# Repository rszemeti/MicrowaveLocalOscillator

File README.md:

# MicrowaveLocalOscillator

[![CC BY-SA 4.0][cc-by-sa-shield]][cc-by-sa]

## Description

A simple 2 stage microwave local oscillator using an ADF 4153 to control a Crystek (or similar) VCO

A OCXO reference oscillator is optionally controlled by an ADF4001 when a 10MHz reference signal is present.

## License 

This work is licensed under a
[Creative Commons Attribution-ShareAlike 4.0 International License][cc-by-sa].

[![CC BY-SA 4.0][cc-by-sa-image]][cc-by-sa]

[cc-by-sa]: http://creativecommons.org/licenses/by-sa/4.0/
[cc-by-sa-image]: https://licensebuttons.net/l/by-sa/4.0/88x31.png
[cc-by-sa-shield]: https://img.shields.io/badge/License-CC%20BY--SA%204.0-lightgrey.svg

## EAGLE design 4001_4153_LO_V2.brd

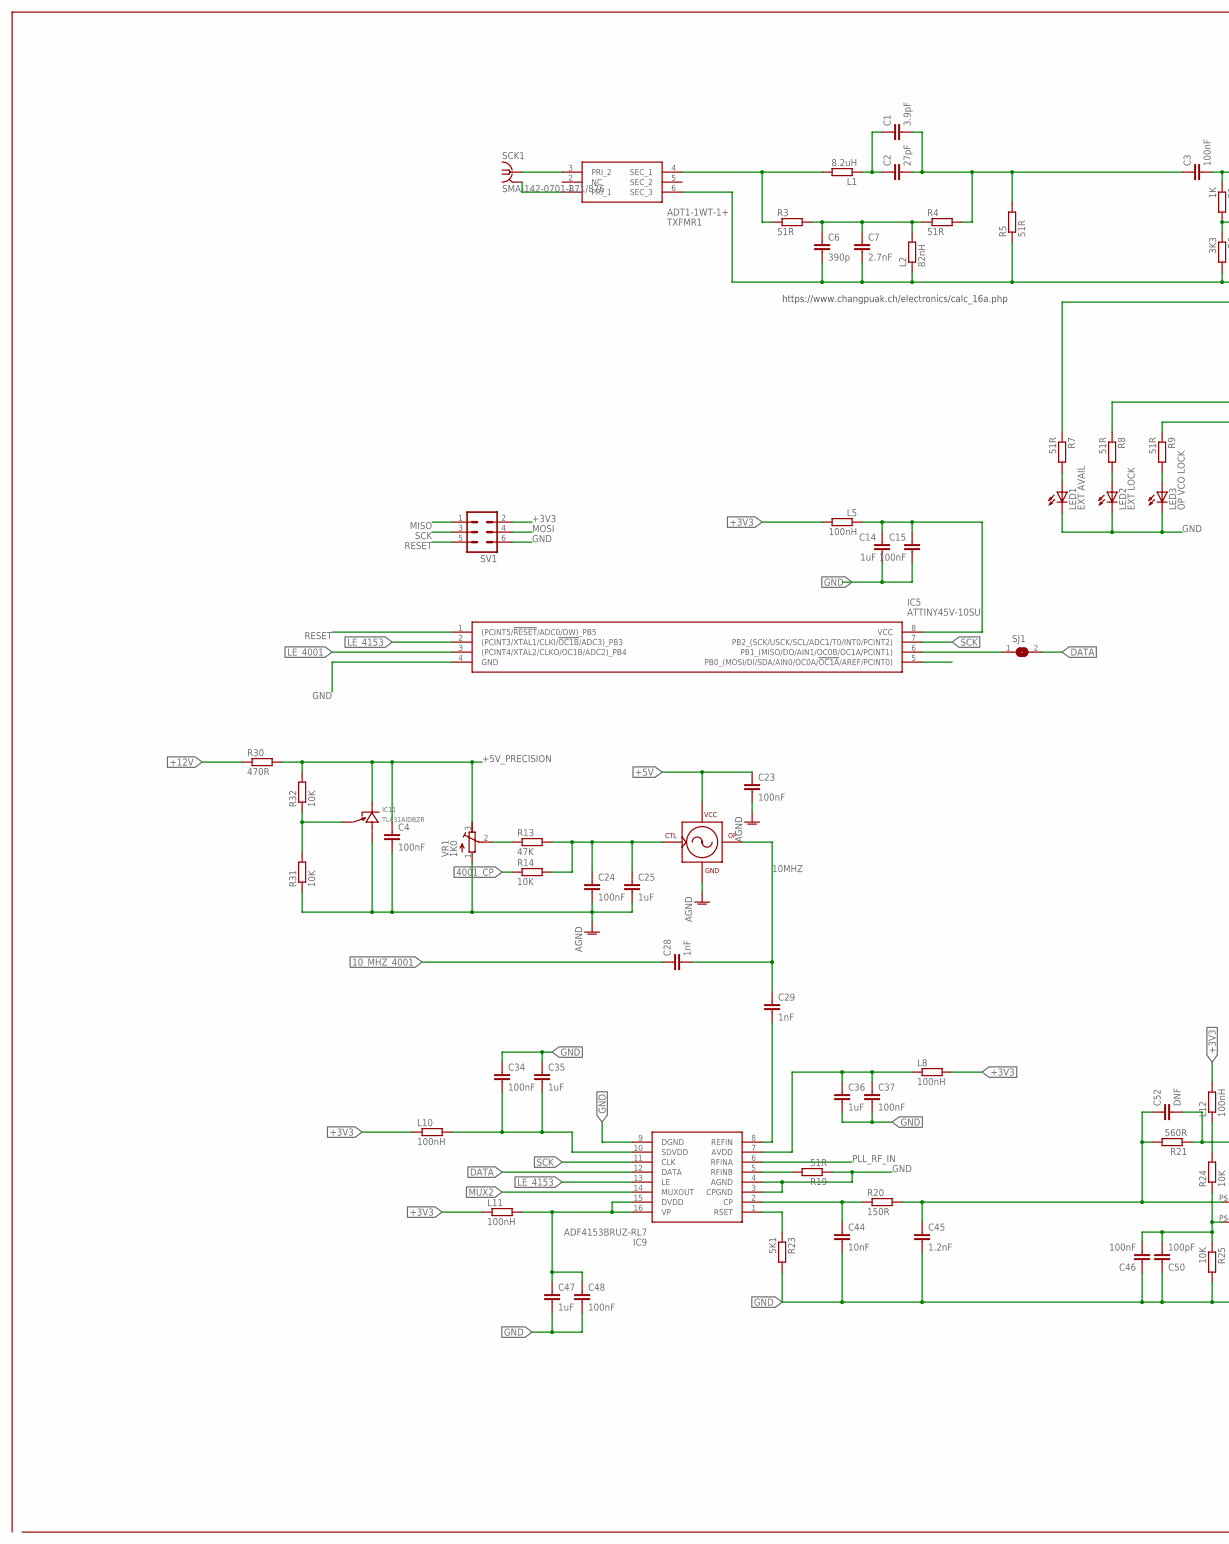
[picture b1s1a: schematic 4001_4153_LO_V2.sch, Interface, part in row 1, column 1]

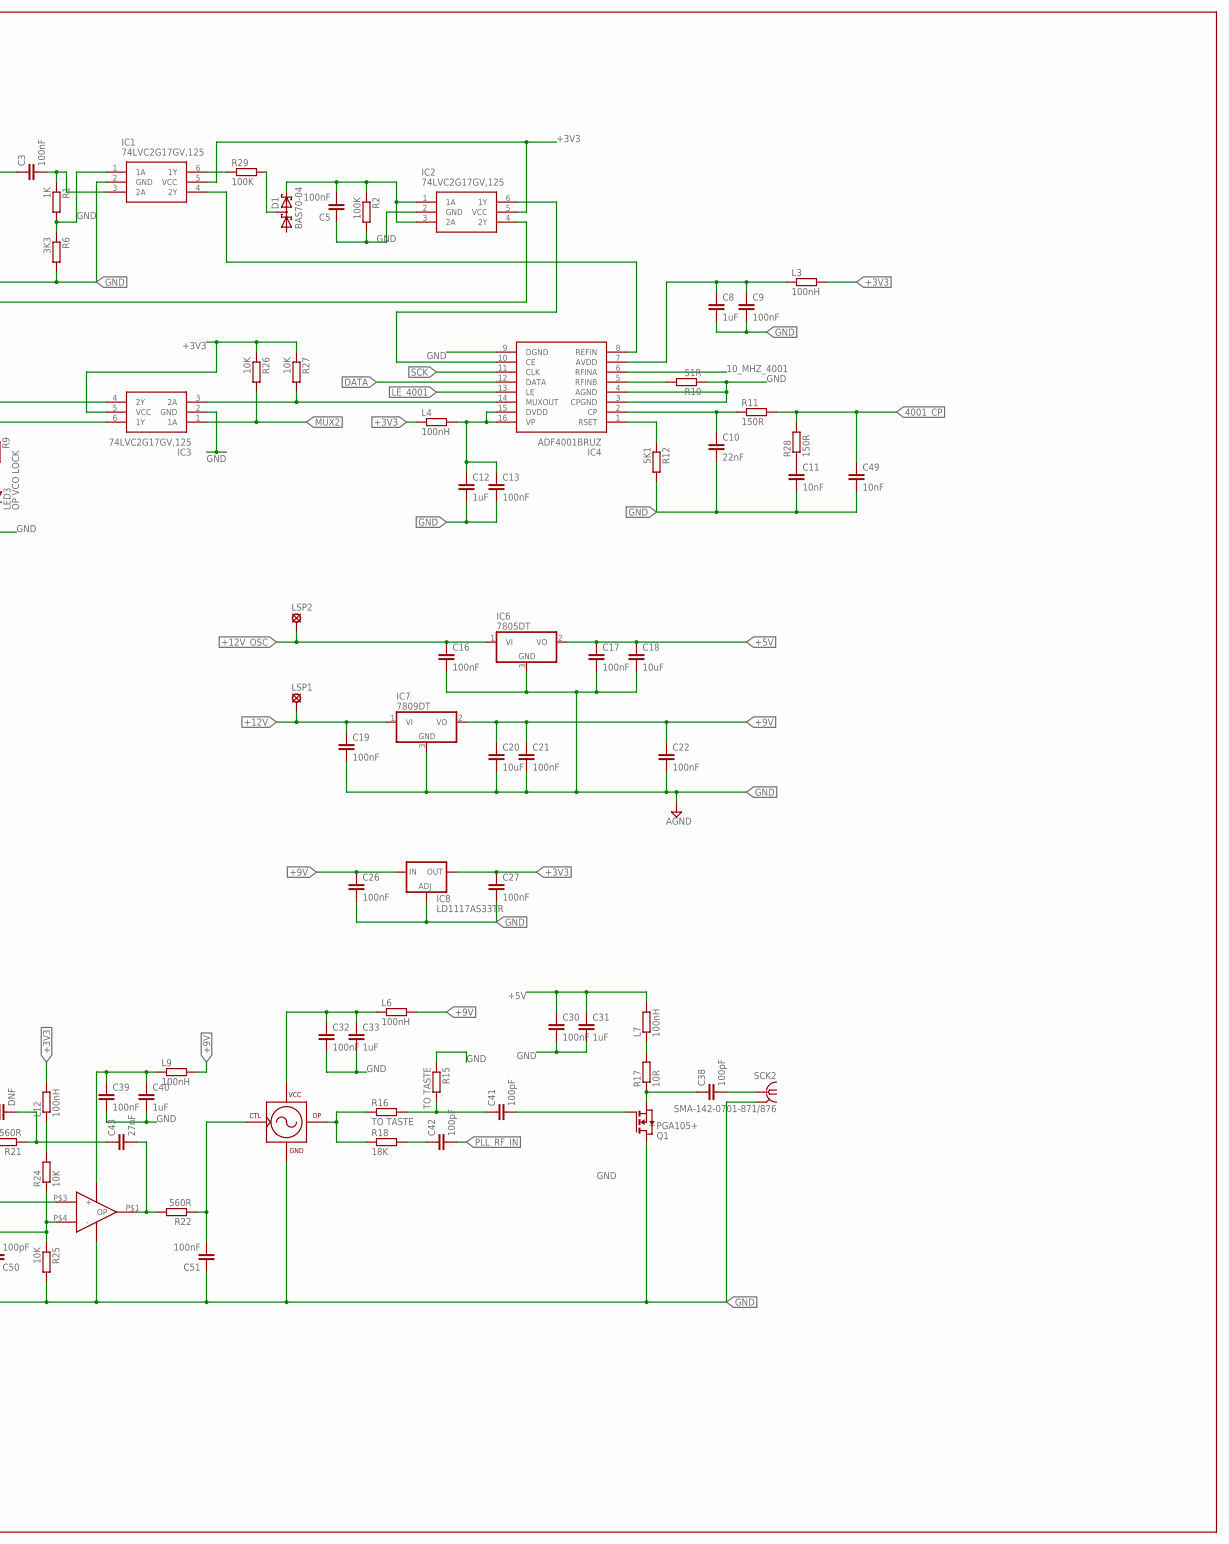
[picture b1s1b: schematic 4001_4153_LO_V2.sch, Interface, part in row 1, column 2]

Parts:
C1: 3.9pF; C0603
C2: 27pF; C0603
C3, C4, C5, C9, C13, C15, C23, C24, C30, C32, C34, C37, C39, C46, C48, C51: 100nF; C0603
C6: 390p; C0603
C7: 2.7nF; C0603
C8, C12, C14, C25, C31, C33, C35, C36, C40, C47: 1uF; C0603
C10: 22nF; C0603
C11, C44, C49: 10nF; C0603
C16, C17, C19, C21, C22, C26, C27: 100nF; C0805
C18, C20: 10uF; C0805
C28, C29: 1nF; C0603
C38, C41, C42, C50: 100pF; C0603
C43: 27nF; C0603
C45: 1.2nF; C0603
C52: DNF; C0603
D1: BAS70-04; SOT23
IC1: 74LVC2G17GV,125; SOT95P275X110-6N
IC2, IC3: 74LVC2G17GV,125; SOT95P275X110-6N; MANUFACTURER_PART_NUMBER 74LVC2G17GV,125; MOUSER_PART_NUMBER 771-74LVC2G17GV-G
IC4: ADF4001BRUZ; SOP65P640X120-16N; JLC C207717
IC5: ATTINY45V-10SU; SOIC127P798X216-8N
IC6: 7805DT; TO252
IC7: 7809DT; TO252
IC8: LD1117AS33TR; SOT223; JLC C108495
IC9: ADF4153BRUZ-RL7; SOP65P640X120-16N
IC10: MCP6H01T-E/LT; SOT23-5; MPN MCP6H01T-E/LT
IC11: TL431AIDBZR; SOT23L
L1: 8.2uH; R0603
L2: 82nH; R0603
L3, L4, L5, L6, L7, L8, L9, L10, L11, L12: 100nH; R0603
LED1: EXT AVAIL; LED3MM
LED2: EXT LOCK; LED3MM
LED3: OP VCO LOCK; LED3MM
LSP1, LSP2: LSP13
OSC1: CTI_OSC
OSC2: CRSYTELEK_127; CRYSTEK_VCO
Q1: PGA105+; SOT89
R1: 1K; R0603
R2, R29: 100K; R0603
R3, R4, R5, R7, R8, R9, R10, R19: 51R; R0603
R6: 3K3; R0603
R11, R20, R28: 150R; R0603
R12, R23: 5K1; R0603
R13: 47K; R0603
R14, R24, R25, R26, R27, R31, R32: 10K; R0603
R15, R16: TO TASTE; R0603
R17: 10R; R0603
R18: 18K; R0603
R21, R22: 560R; R0603
R30: 470R; R0603
SCK1: SMA-142-0701-871/876; J502-ND-142-0701-871/876
SCK2: SMA-142-0701-871/876; J502-ND-142-0701-871/876; MPN 142-0701-871
SJ1: SJ
SV1: ML6; MPN MC-254-06-00-ST-DIP
TXFMR1: ADT1-1WT-1+; SOP254P691X284-6N
VR1: 1K0; RTRIM64Y; MPN 3296Y-1-103LF

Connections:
10MHZ: C28.2, C29.1, OSC1.OUT (OP)
10MHZ_REF: C29.2, IC9.8 (REFIN)
10_MHZ_4001: C28.1, IC4.6 (RFINA)
4001_CP: C49.1, R11.2, R14.1, R28.2
+3V3: C27.1, IC1.5 (VCC), IC2.5 (VCC), IC3.5 (VCC), IC8.4 (OUT), L3.2, L4.1, L5.2, L8.2, L10.1, L11.1, L12.2, R26.1, R27.1, SV1.2
+5V: C17.1, C18.1, C23.1, C30.1, C31.1, IC6.2 (VO), L7.2, OSC1.VCC
+5V_PRECISION: C4.1, IC11.G (CATHODE), R30.2, R32.2, VR1.3 (A)
+8V: C32.1, C33.1, L6.1, OSC2.P$14 (VCC)
+9V: C20.1, C21.1, C22.1, C26.1, IC7.2 (VO), IC8.3 (IN), L6.2, L9.2
+12V: C19.1, IC7.1 (VI), LSP1.MP, R30.1
+12V_OSC: C16.1, IC6.1 (VI), LSP2.MP
AVDD: C36.1, C37.1, IC9.7 (AVDD), L8.1
DATA: IC4.12 (DATA), IC9.12 (DATA), SJ1.2
DVDD: C47.1, C48.1, IC9.15 (DVDD), IC9.16 (VP), L11.2
DVDD1: C12.1, C13.1, IC4.15 (DVDD), IC4.16 (VP), L4.2
FILT_EXT_REF: C1.2, C2.2, C3.1, R4.2, R5.2
GND: C4.2, C5.1, C6.2, C7.2, C8.2, C9.2, C10.2, C11.2, C12.2, C13.2, C14.2, C15.2, C16.2, C17.2, C18.2, C19.2, C20.2, C21.2, C22.2, C23.2, C24.2, C25.2, C26.2, C27.2, C30.2, C31.2, C32.2, C33.2, C34.1, C35.1, C36.2, C37.2, C39.2, C40.2, C44.2, C45.2, C46.1, C47.2, C48.2, C49.2, C50.1, C51.1, IC1.2 (GND), IC2.2 (GND), IC3.2 (GND), IC4.3 (CPGND), IC4.4 (AGND), IC4.9 (DGND), IC5.4 (GND), IC6.3 (GND), IC7.3 (GND), IC8.1 (ADJ), IC9.3 (CPGND), IC9.4 (AGND), IC9.9 (DGND), IC10.P$2 (-VE), IC11.D (ANODE), L2.1, LED1.K (C), LED2.K (C), LED3.K (C), OSC1.GND, OSC2.P$1 (GND), OSC2.P$3 (GND), OSC2.P$4 (GND), OSC2.P$5 (GND), OSC2.P$6 (GND), OSC2.P$7 (GND), OSC2.P$8 (GND), OSC2.P$9 (GND), OSC2.P$11 (GND), OSC2.P$12 (GND), OSC2.P$13 (GND), OSC2.P$15 (GND), OSC2.P$16 (GND), Q1.2 (D), R2.2, R5.1, R6.2, R10.1, R12.2, R15.1, R19.1, R23.2, R25.2, R31.1, SCK1.G@1 (GND), SCK1.G@2 (GND), SCK1.G@3 (GND), SCK1.G@4 (GND), SCK2.G@1 (GND), SCK2.G@2 (GND), SCK2.G@3 (GND), SCK2.G@4 (GND), SV1.6, TXFMR1.1 (PRI_1), TXFMR1.6 (SEC_3), VR1.1 (E)
LE_4001: IC4.13 (LE), IC5.3 ((PCINT4/XTAL2/CLKO/OC1B/ADC2)_PB4)
LE_4153: IC5.2 ((PCINT3/XTAL1/CLKI/!OC1B!/ADC3)_PB3), IC9.13 (LE)
LOOP_IN: C45.1, C52.1, IC10.P$3 (+), R20.2, R21.2
MISO: IC5.6 (PB1_(MISO/DO/AIN1/OC0B/OC1A/PCINT1)), SJ1.1, SV1.1
MOSI: IC5.5 (PB0_(MOSI/DI/SDA/AIN0/OC0A/!OC1A!/AREF/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), SV1.4
MUX2: IC3.1 (1A), IC9.14 (MUXOUT), R26.2
unnamed: IC9.5 (RFINB), R19.2
unnamed: IC9.1 (RSET), R23.1
unnamed: C39.1, C40.1, IC10.P$6 (+VE), L9.1
unnamed: OSC2.P$10 (OP), R16.1, R18.1
unnamed: C46.2, C50.2, IC10.P$4 (-), R24.1, R25.1
unnamed: IC4.5 (RFINB), R10.2
unnamed: C43.1, C52.2, R21.1
unnamed: C43.2, IC10.P$1 (OP), R22.2
unnamed: C42.1, R18.2
unnamed: C41.2, Q1.1 (G)
unnamed: C38.1, Q1.3 (S), R17.1
unnamed: C41.1, R15.2, R16.2
unnamed: IC4.1 (RSET), R12.1
unnamed: C10.1, IC4.2 (CP), R11.1
unnamed: C44.1, IC9.2 (CP), R20.1
unnamed: C3.2, IC1.3 (2A), R1.1
unnamed: LED3.A, R9.2
unnamed: R13.1, VR1.2 (S)
unnamed: IC3.4 (2Y), R8.1
unnamed: L7.1, R17.2
unnamed: C11.1, R28.1
unnamed: D1.3 (C1A2), R29.2
unnamed: C5.2, D1.2 (C2), IC2.1 (1A), IC2.3 (2A), R2.1
unnamed: LED2.A, R8.2
unnamed: IC3.3 (2A), IC4.14 (MUXOUT), R27.2
unnamed: IC3.6 (1Y), R9.1
unnamed: LED1.A, R7.2
unnamed: IC2.4 (2Y), R7.1
unnamed: IC1.6 (1Y), R29.1
unnamed: C1.1, C2.1, L1.1
unnamed: C24.1, C25.1, OSC1.REF (CTRL), R13.2, R14.2
unnamed: L1.2, R3.1, TXFMR1.4 (SEC_1)
unnamed: SCK1.1, TXFMR1.3 (PRI_2)
unnamed: C6.1, C7.1, L2.2, R3.2, R4.1
unnamed: C8.1, C9.1, IC4.7 (AVDD), L3.1
unnamed: IC1.1 (1A), R1.2, R6.1
unnamed: IC1.4 (2Y), IC4.8 (REFIN)
unnamed: L12.1, R24.2
unnamed: C51.2, OSC2.P$2 (CTRL), R22.1
unnamed: IC11.S (CTRL), R31.2, R32.1
OUTPUT: C38.2, SCK2.1
PLL_RF_IN: C42.2, IC9.6 (RFINA)
RESET: IC5.1 ((PCINT5/!RESET!/ADC0/DW)_PB5), SV1.5
SCK: IC4.11 (CLK), IC5.7 (PB2_(SCK/USCK/SCL/ADC1/T0/INT0/PCINT2)), IC9.11 (CLK), SV1.3
SDVDD: C34.2, C35.2, IC9.10 (SDVDD), L10.2
SDVDD1: IC2.6 (1Y), IC4.10 (CE)
VCC_UP: C14.1, C15.1, IC5.8 (VCC), L5.1

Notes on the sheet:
https://www.changpuak.ch/electronics/calc_16a.php

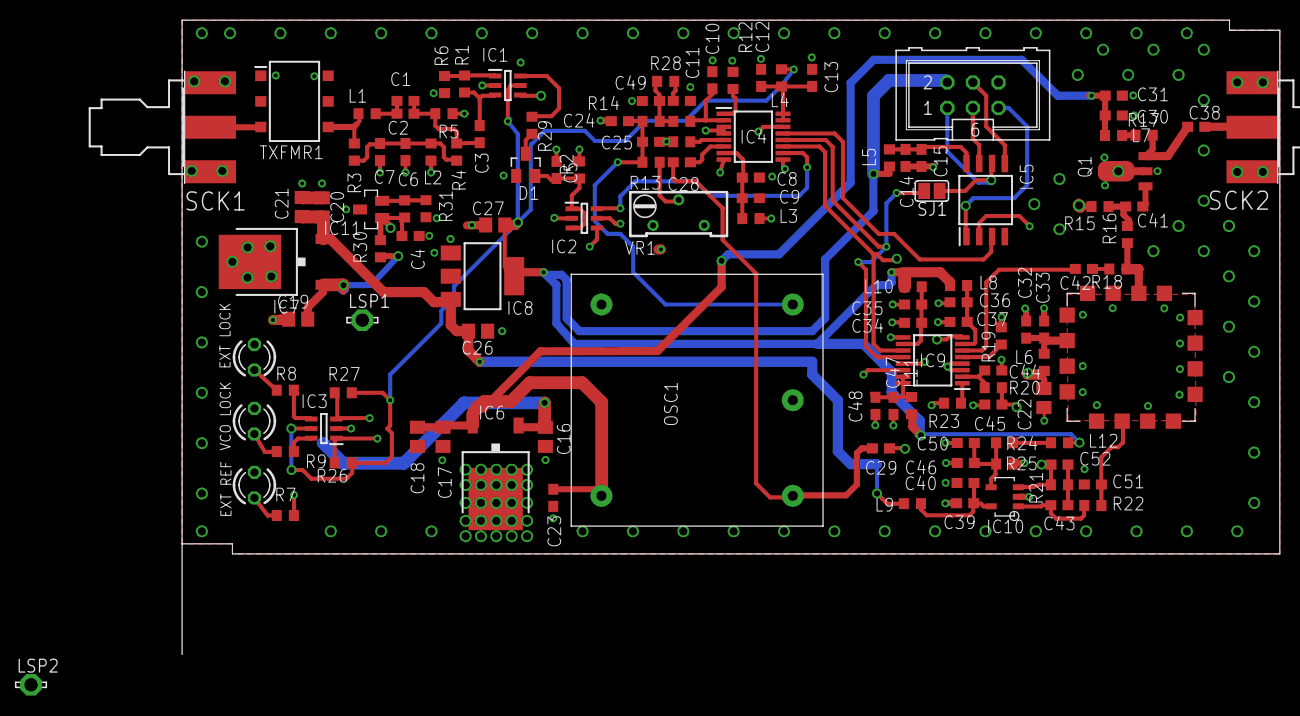
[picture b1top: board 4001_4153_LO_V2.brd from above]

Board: 4 copper layers, 109.0 x 53.0 mm, 122 parts (0 on the bottom side), 70 nets.

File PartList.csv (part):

Partlist

Exported from 4001_4153_LO_V2.brd at 26/11/2022 21:42:16

EAGLE Version 6.2.0 Copyright (c) 1988-2012 CadSoft

Assembly variant: 

Part     Value                Package                  Library         Position (mm)         Orientation

C1       3.9pF                C0603                    resistor        (22.184 44.983)       R0
C2       27pF                 C0603                    resistor        (22.184 43.713)       R0
C3       100nF                C0603                    resistor        (29.55 41.681)        R90
C5       100nF                C0603                    resistor        (37.17 38.125)        R270
C6       390p                 C0603                    resistor        (22.184 39.903)       R270
C7       2.7nF                C0603                    resistor        (19.644 39.903)       R270
C8       1uF                  C0603                    resistor        (56.474 37.363)       R0
C9       100nF                C0603                    resistor        (56.474 35.331)       R0
C10      22nF                 C0603                    resistor        (52.6538 47.031)      R90
C11      10nF                 C0603                    resistor        (49.616 44.983)       R0
C12      1uF                  C0603                    resistor        (57.49 47.269)        R90
C13      100nF                C0603                    resistor        (62.554 47.269)       R90
C14      1uF                  C0603                    resistor        (71.823 39.3165)      R270
C15      100nF                C0603                    resistor        (73.4105 39.3165)     R270
C16      100nF                C0805                    rcl             (36.07 11.625)        R270
C17      100nF                C0805                    rcl             (25.91 11.625)        R270
C18      10uF                 C0805                    rcl             (23.37 11.625)        R270
C19      100nF                C0805                    rcl             (14.219796875 22.414459375) R270
C20      10uF                 C0805                    rcl             (19.40608125 23.082025) R0
C21      100nF                C0805                    rcl             (19.442696875 25.072253125) R0
C22      100nF                C0805                    rcl             (85.571778125 15.481146875) R270
C23      100nF                C0603                    rcl             (49.6414 30.2002)     R180
C24      100nF                C0603                    rcl             (43.47164375 42.96926875) R180
C25      1uF                  C0603                    rcl             (46.568 40.919)       R0
C26      100nF                C0805                    rcl             (29.389134375 22.11664375) R0
C27      100nF                C0805                    rcl             (31.09234375 32.661259375) R180
C28      1nF                  C0603                    resistor        (49.616 38.887)       R180
C29      1nF                  C0603                    resistor        (78.607853125 11.519221875) R180
C30      100nF                C0603                    resistor        (92.5032375 43.536478125) R0
C31      1uF                  C0603                    resistor        (92.511296875 45.5050375) R0
C32      100nF                C0603                    resistor        (83.816090625 22.27368125) R90
C33      1uF                  C0603                    resistor        (85.58979375 22.28625625) R90
C34      100nF                C0603                    resistor        (72.587615625 22.950003125) R0
C35      1uF                  C0603                    resistor        (72.59211875 24.756921875) R0
C36      1uF                  C0603                    resistor        (77.10156875 24.97775) R180
C37      100nF                C0603                    resistor        (77.104415625 23.03903125) R180
C38      100pF                C0603                    resistor        (100.6980125 42.4133375) R0
C39      100nF                C0603                    resistor        (98.269059375 8.22005625) R0
C40      1uF                  C0603                    resistor        (98.29523125 9.993734375) R0
C41      100pF                C0603                    resistor        (94.5482 34.492921875) R0
C42      100pF                C0603                    resistor        (89.541459375 28.29810625) R180
C43      6.8nF                C0603                    resistor        (88.940515625 8.28975625) R0
C44      22nF                 C0603                    resistor        (80.545046875 18.214171875) R0
C45      10nF                 C0603                    resistor        (80.551871875 14.826984375) R180
C46      15nF                 C0603                    resistor        (88.93343125 4.39005) R0
C47      1uF                  C0603                    resistor        (70.62865625 14.704671875) R270
C48      100nF                C0603                    resistor        (68.841971875 14.70188125) R270
C49      10nF                 C0603                    resistor        (46.5468 44.971)      R180
D1       BAS70-04             SOT23                    diode           (34.122 38.633)       R0
IC1      74LVC2G17GV,125      SOT95P275X110-6N         74LVC2G17GV_125 (32.344 46.507)       R0
IC2      74LVC2G17GV,125      SOT95P275X110-6N         74LVC2G17GV_125 (39.946 33.323)       R0
IC3      74LVC2G17GV,125      SOT95P275X110-6N         74LVC2G17GV_125 (14.074 12.447)       R180
IC4      ADF4001BRUZ          SOP65P640X120-16N        ADF4001BRUZ     (56.728 41.427)       R0
IC5      ATTINY45V-10SU       SOIC127P798X216-8N       ATTINY45V-10SU  (79.79 35.137)        R90
IC6      7805DT               TO252                    linear          (31.136 7.947)        R180
IC7      7809DT               TO252                    linear          (13.994 27.759)       R0
IC8      LD1117AS33TR         SOT223                   v-reg           (29.83038125 27.5757625) R270
IC9      ADF4153BRUZ-RL7      SOP65P640X120-16N        ADF4153BRUZ-RL7 (74.531103125 19.22043125) R180
IC10     MCP6H01              SOT23-5                  RF              (94.32 7.3275)        R0
L1       8.2uH                R0603                    resistor        (18.374 43.713)       R180
L2       82nH                 R0603                    resistor        (24.724 39.903)       R90
L3       100nH                R0603                    resistor        (56.474 33.299)       R0
L4       100nH                R0603                    resistor        (59.522 47.269)       R270
L5       100nH                R0603                    resistor        (70.2355 39.3165)     R270
L6       100nH                R0603                    resistor        (85.601953125 19.025) R270
L7       100nH                R0603                    resistor        (92.484778125 41.541925) R180
L8       100nH                R0603                    resistor        (77.094775 26.646446875) R180
L9       100nH                R0603                    resistor        (98.232809375 5.972478125) R0
L10      100nH                R0603                    resistor        (72.5892375 26.526909375) R0
L11      100nH                R0603                    resistor        (72.418071875 14.728709375) R90
LED1     EXT AVAIL            LED3MM                   led             (7.184 6.827)         R90
LED2     EXT LOCK             LED3MM                   led             (7.184 19.527)        R90
LED3     OP VCO LOCK          LED3MM                   led             (7.184 13.177)        R90
LSP1     LSP13                LSP13                    solpad          (7.42 26.695)         R0
OSC1     CTI_OSC              CTI_OSC                  RF              (51.14 15.265)        R90
OSC2     CRSYTELEK_127        CRYSTEK_VCO              RF              (87.880125 13.1765375) R0
Q1       PGA105+              SOT89                    zetex           (93.685 37.998)       R90
R1       1K                   R0603                    rcl             (28.04 46.663)        R90
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
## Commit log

2022-11-25 Add files via upload
    Initial Commit
2022-11-25 Size change and pre-release tweaks
    Updated sizes, sorted out component name positions on PCB, added 10R to PGA105+drive ref Andy JNT
2022-11-25 Renumber
    Renumbered all components
2022-11-25 Removed backup files
    ...
2022-11-25 Gerbers for test boards
    Layer stack sorted out, gerbers produced in JLC format
2022-11-26 Misc circuit revisions
    Updated loop filter on 4001, added pullups to MUXOUT
2022-11-26 Create .gitignore
    Ignore Eagle backup files
2022-11-26 test gitignore
2022-11-26 remove backups
    ...
2022-11-26 Minor mods
    Added text to rear silk,
    moved a few components around the 4001 loop filter
2022-11-26 Soldering mods
    Moved components to clear board edges on underside for soldering to box.
2022-11-26 Thermal mods
    Rotated 5V reg, ref GM4ISM
2022-11-26 Tracking
    Rotated 5v reg
    tracking around output device
2022-11-26 Output and detector
    Moved resistor in output stage to power feed
    Swapped C for R in 10MHz detector
2022-11-26 multi-turn
    replaced single turn pot with multiturn
2022-11-26 Tracking corrections
    Minor clearance issues
2022-11-26 JLC Release
2022-11-26 Update README.md
    spelling ...
2022-11-26 JLC Production files added
    The files in the "JLC" folder can be uploaded to the JLC PCBA service to get a pretty complete PCB ...
2022-11-30 JLC release
    As issued to JLC
2022-12-01 Update 4001_4153_LO_V2.pdf
    JLC release schematic
2023-09-09 various
2023-09-09 filter loop update
2023-09-09 Layout
2023-09-10 Photos
2023-09-11 Ref synth updates
    Firmware working for ADF4001
    Various board updates, ref input still needs works
2026-01-13 catchup
2026-03-17 misc

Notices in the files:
parts and their libraries:
Document: This design is licensed under a Creative Commons Attribution-ShareAlike
Document: 3.0 Unported License: http://creativecommons.org/licenses/by-sa/3.0
